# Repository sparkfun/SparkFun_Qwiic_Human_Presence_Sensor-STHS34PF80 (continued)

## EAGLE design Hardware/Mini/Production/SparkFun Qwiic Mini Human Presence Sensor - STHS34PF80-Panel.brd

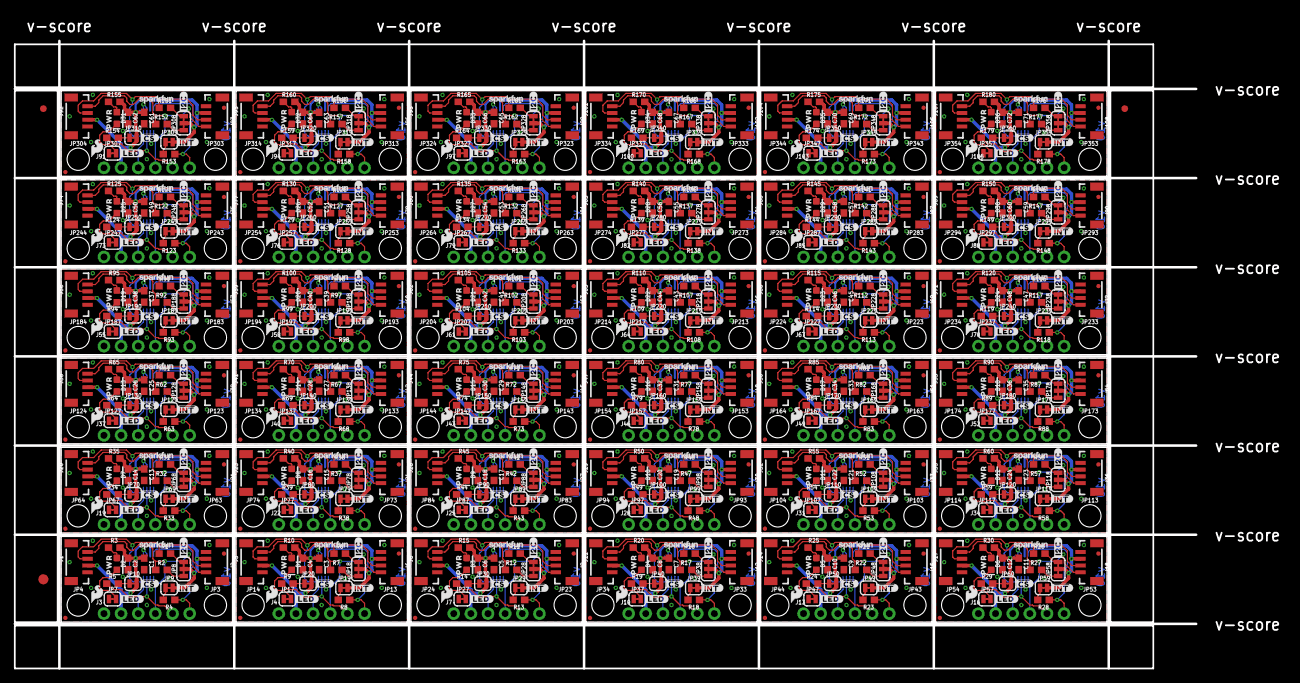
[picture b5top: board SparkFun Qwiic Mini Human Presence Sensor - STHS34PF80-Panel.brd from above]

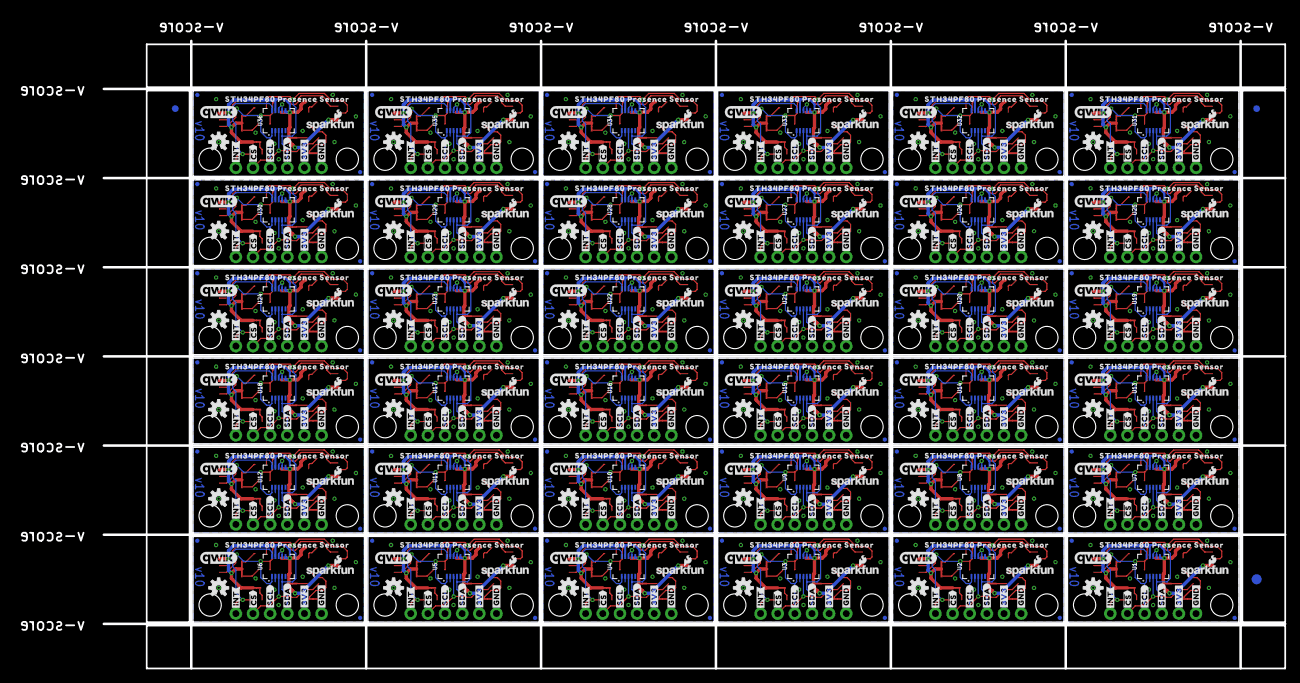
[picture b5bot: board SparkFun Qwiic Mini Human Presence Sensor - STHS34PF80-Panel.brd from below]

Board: 2 copper layers, 175.0 x 93.0 mm, 1410 parts (471 on the bottom side), 432 nets.

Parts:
C1, C3, C5, C7, C9, C11, C13, C15, C17, C19, C21, C23, C25, C27, C29, C31, C33, C35, C37, C39, C41, C43, C45, C47, C49, C51, C53, C55, C57, C59, C61, C63, C65, C67, C69, C71: 1.0uF; 0603
C2, C4, C6, C8, C10, C12, C14, C16, C18, C20, C22, C24, C26, C28, C30, C32, C34, C36, C38, C40, C42, C44, C46, C48, C50, C52, C54, C56, C58, C60, C62, C64, C66, C68, C70, C72: 0.1uF; 0603
D1, D2, D3, D4, D5, D6, D7, D8, D9, D10, D11, D12, D13, D14, D15, D16, D17, D18, D19, D20, D21, D22, D23, D24, D25, D26, D27, D28, D29, D30, D31, D32, D33, D34, D35, D36: RED; LED-0603
E$1, E$2, E$3, E$4: FIDUCIAL-1X2
E$5, E$6: FIDUCIAL-1.5X3
J1, J2, J5, J6, J8, J9, J11, J12, J14, J15, J17, J18, J20, J21, J23, J24, J26, J27, J29, J30, J32, J33, J35, J36, J38, J39, J41, J42, J44, J45, J47, J48, J50, J51, J53, J54, J56, J57, J59, J60, J62, J63, J65, J66, J68, J69, J71, J72, J74, J75, J77, J78, J80, J81, J83, J84, J86, J87, J89, J90, J92, J93, J95, J96, J98, J99, J101, J102, J104, J105, J107, J108: Vertical Qwiic Connector; JST04_1MM_VERT
J3, J4, J7, J10, J13, J16, J19, J22, J25, J28, J31, J34, J37, J40, J43, J46, J49, J52, J55, J58, J61, J64, J67, J70, J73, J76, J79, J82, J85, J88, J91, J94, J97, J100, J103, J106: 1X06_NO_SILK
JP1, JP2, JP5, JP6, JP11, JP12, JP15, JP16, JP21, JP22, JP25, JP26, JP31, JP32, JP35, JP36, JP41, JP42, JP45, JP46, JP51, JP52, JP55, JP56, JP61, JP62, JP65, JP66, JP71, JP72, JP75, JP76, JP81, JP82, JP85, JP86, JP91, JP92, JP95, JP96, JP101, JP102, JP105, JP106, JP111, JP112, JP115, JP116, JP121, JP122, JP125, JP126, JP131, JP132, JP135, JP136, JP141, JP142, JP145, JP146, JP151, JP152, JP155, JP156, JP161, JP162, JP165, JP166, JP171, JP172, JP175, JP176, JP181, JP182, JP185, JP186, JP191, JP192, JP195, JP196, JP201, JP202, JP205, JP206, JP211, JP212, JP215, JP216, JP221, JP222, JP225, JP226, JP231, JP232, JP235, JP236, JP241, JP242, JP245, JP246, JP251, JP252, JP255, JP256, JP261, JP262, JP265, JP266, JP271, JP272, JP275, JP276, JP281, JP282, JP285, JP286, JP291, JP292, JP295, JP296, JP301, JP302, JP305, JP306, JP311, JP312, JP315, JP316, JP321, JP322, JP325, JP326, JP331, JP332, JP335, JP336, JP341, JP342, JP345, JP346, JP351, JP352, JP355, JP356: FIDUCIALUFIDUCIAL; FIDUCIAL-MICRO
JP3, JP4, JP13, JP14, JP23, JP24, JP33, JP34, JP43, JP44, JP53, JP54, JP63, JP64, JP73, JP74, JP83, JP84, JP93, JP94, JP103, JP104, JP113, JP114, JP123, JP124, JP133, JP134, JP143, JP144, JP153, JP154, JP163, JP164, JP173, JP174, JP183, JP184, JP193, JP194, JP203, JP204, JP213, JP214, JP223, JP224, JP233, JP234, JP243, JP244, JP253, JP254, JP263, JP264, JP273, JP274, JP283, JP284, JP293, JP294, JP303, JP304, JP313, JP314, JP323, JP324, JP333, JP334, JP343, JP344, JP353, JP354: STAND-OFF
JP7, JP9, JP10, JP17, JP19, JP20, JP27, JP29, JP30, JP37, JP39, JP40, JP47, JP49, JP50, JP57, JP59, JP60, JP67, JP69, JP70, JP77, JP79, JP80, JP87, JP89, JP90, JP97, JP99, JP100, JP107, JP109, JP110, JP117, JP119, JP120, JP127, JP129, JP130, JP137, JP139, JP140, JP147, JP149, JP150, JP157, JP159, JP160, JP167, JP169, JP170, JP177, JP179, JP180, JP187, JP189, JP190, JP197, JP199, JP200, JP207, JP209, JP210, JP217, JP219, JP220, JP227, JP229, JP230, JP237, JP239, JP240, JP247, JP249, JP250, JP257, JP259, JP260, JP267, JP269, JP270, JP277, JP279, JP280, JP287, JP289, JP290, JP297, JP299, JP300, JP307, JP309, JP310, JP317, JP319, JP320, JP327, JP329, JP330, JP337, JP339, JP340, JP347, JP349, JP350, JP357, JP359, JP360: JUMPER-SMT_2_NC_TRACE_SILK; SMT-JUMPER_2_NC_TRACE_SILK
JP8, JP18, JP28, JP38, JP48, JP58, JP68, JP78, JP88, JP98, JP108, JP118, JP128, JP138, JP148, JP158, JP168, JP178, JP188, JP198, JP208, JP218, JP228, JP238, JP248, JP258, JP268, JP278, JP288, JP298, JP308, JP318, JP328, JP338, JP348, JP358: JUMPER-SMT_3_2-NC_TRACE_SILK; SMT-JUMPER_3_2-NC_TRACE_SILK
LOGO1, LOGO5, LOGO11, LOGO16, LOGO21, LOGO26, LOGO31, LOGO36, LOGO41, LOGO46, LOGO51, LOGO56, LOGO61, LOGO66, LOGO71, LOGO76, LOGO81, LOGO86, LOGO91, LOGO96, LOGO101, LOGO106, LOGO111, LOGO116, LOGO121, LOGO126, LOGO131, LOGO136, LOGO141, LOGO146, LOGO151, LOGO156, LOGO161, LOGO166, LOGO171, LOGO176: OSHW-LOGOS; OSHW-LOGO-S
LOGO2, LOGO8, LOGO13, LOGO18, LOGO23, LOGO28, LOGO33, LOGO38, LOGO43, LOGO48, LOGO53, LOGO58, LOGO63, LOGO68, LOGO73, LOGO78, LOGO83, LOGO88, LOGO93, LOGO98, LOGO103, LOGO108, LOGO113, LOGO118, LOGO123, LOGO128, LOGO133, LOGO138, LOGO143, LOGO148, LOGO153, LOGO158, LOGO163, LOGO168, LOGO173, LOGO178: SFE_LOGO_NAME_FLAME7_MM; SFE_LOGO_NAME_FLAME_7MM
LOGO3, LOGO7, LOGO12, LOGO17, LOGO22, LOGO27, LOGO32, LOGO37, LOGO42, LOGO47, LOGO52, LOGO57, LOGO62, LOGO67, LOGO72, LOGO77, LOGO82, LOGO87, LOGO92, LOGO97, LOGO102, LOGO107, LOGO112, LOGO117, LOGO122, LOGO127, LOGO132, LOGO137, LOGO142, LOGO147, LOGO152, LOGO157, LOGO162, LOGO167, LOGO172, LOGO177: QWIIC_LOGO_CONNECTOR; QWIIC_5.5MM
LOGO4, LOGO10, LOGO15, LOGO20, LOGO25, LOGO30, LOGO35, LOGO40, LOGO45, LOGO50, LOGO55, LOGO60, LOGO65, LOGO70, LOGO75, LOGO80, LOGO85, LOGO90, LOGO95, LOGO100, LOGO105, LOGO110, LOGO115, LOGO120, LOGO125, LOGO130, LOGO135, LOGO140, LOGO145, LOGO150, LOGO155, LOGO160, LOGO165, LOGO170, LOGO175, LOGO180: SFE_LOGO_NAME5_MM; SFE_LOGO_NAME_5MM
LOGO6, LOGO9, LOGO14, LOGO19, LOGO24, LOGO29, LOGO34, LOGO39, LOGO44, LOGO49, LOGO54, LOGO59, LOGO64, LOGO69, LOGO74, LOGO79, LOGO84, LOGO89, LOGO94, LOGO99, LOGO104, LOGO109, LOGO114, LOGO119, LOGO124, LOGO129, LOGO134, LOGO139, LOGO144, LOGO149, LOGO154, LOGO159, LOGO164, LOGO169, LOGO174, LOGO179: SFE_LOGO_FLAME.1_INCH; SFE_LOGO_FLAME_.1
R1, R2, R6, R7, R11, R12, R16, R17, R21, R22, R26, R27, R31, R32, R36, R37, R41, R42, R46, R47, R51, R52, R56, R57, R61, R62, R66, R67, R71, R72, R76, R77, R81, R82, R86, R87, R91, R92, R96, R97, R101, R102, R106, R107, R111, R112, R116, R117, R121, R122, R126, R127, R131, R132, R136, R137, R141, R142, R146, R147, R151, R152, R156, R157, R161, R162, R166, R167, R171, R172, R176, R177: 2.2k; 0603
R3, R10, R15, R20, R25, R30, R35, R40, R45, R50, R55, R60, R65, R70, R75, R80, R85, R90, R95, R100, R105, R110, R115, R120, R125, R130, R135, R140, R145, R150, R155, R160, R165, R170, R175, R180: 4.7k; 0603
R4, R5, R8, R9, R13, R14, R18, R19, R23, R24, R28, R29, R33, R34, R38, R39, R43, R44, R48, R49, R53, R54, R58, R59, R63, R64, R68, R69, R73, R74, R78, R79, R83, R84, R88, R89, R93, R94, R98, R99, R103, R104, R108, R109, R113, R114, R118, R119, R123, R124, R128, R129, R133, R134, R138, R139, R143, R144, R148, R149, R153, R154, R158, R159, R163, R164, R168, R169, R173, R174, R178, R179: 10k; 0603
U1, U2, U3, U4, U5, U6, U7, U8, U9, U10, U11, U12, U13, U14, U15, U16, U17, U18, U19, U20, U21, U22, U23, U24, U25, U26, U27, U28, U29, U30, U31, U32, U33, U34, U35, U36: STHS34PF80; OLGA-10L
U$1, U$22, U$34, U$46, U$58, U$70, U$82, U$94, U$106, U$118, U$130, U$142, U$154, U$166, U$178, U$190, U$202, U$214, U$226, U$238, U$250, U$262, U$274, U$286, U$298, U$310, U$322, U$334, U$346, U$358, U$370, U$382, U$394, U$406, U$418, U$430: #3V3#36
U$2, U$23, U$35, U$47, U$59, U$71, U$83, U$95, U$107, U$119, U$131, U$143, U$155, U$167, U$179, U$191, U$203, U$215, U$227, U$239, U$251, U$263, U$275, U$287, U$299, U$311, U$323, U$335, U$347, U$359, U$371, U$383, U$395, U$407, U$419, U$431: ##CS#36
U$3, U$6, U$25, U$37, U$49, U$61, U$73, U$85, U$97, U$109, U$121, U$133, U$145, U$157, U$169, U$181, U$193, U$205, U$217, U$229, U$241, U$253, U$265, U$277, U$289, U$301, U$313, U$325, U$337, U$349, U$361, U$373, U$385, U$397, U$409, U$421: #SDA#5
U$4, U$14, U$26, U$38, U$50, U$62, U$74, U$86, U$98, U$110, U$122, U$134, U$146, U$158, U$170, U$182, U$194, U$206, U$218, U$230, U$242, U$254, U$266, U$278, U$290, U$302, U$314, U$326, U$338, U$350, U$362, U$374, U$386, U$398, U$410, U$422: #SCL#6
U$5, U$24, U$36, U$48, U$60, U$72, U$84, U$96, U$108, U$120, U$132, U$144, U$156, U$168, U$180, U$192, U$204, U$216, U$228, U$240, U$252, U$264, U$276, U$288, U$300, U$312, U$324, U$336, U$348, U$360, U$372, U$384, U$396, U$408, U$420, U$432: #INT#37
U$7, U$15, U$27, U$39, U$51, U$63, U$75, U$87, U$99, U$111, U$123, U$135, U$147, U$159, U$171, U$183, U$195, U$207, U$219, U$231, U$243, U$255, U$267, U$279, U$291, U$303, U$315, U$327, U$339, U$351, U$363, U$375, U$387, U$399, U$411, U$423: PWR9
U$8, U$16, U$28, U$40, U$52, U$64, U$76, U$88, U$100, U$112, U$124, U$136, U$148, U$160, U$172, U$184, U$196, U$208, U$220, U$232, U$244, U$256, U$268, U$280, U$292, U$304, U$316, U$328, U$340, U$352, U$364, U$376, U$388, U$400, U$412, U$424: #I2C#0
U$9, U$17, U$29, U$41, U$53, U$65, U$77, U$89, U$101, U$113, U$125, U$137, U$149, U$161, U$173, U$185, U$197, U$209, U$221, U$233, U$245, U$257, U$269, U$281, U$293, U$305, U$317, U$329, U$341, U$353, U$365, U$377, U$389, U$401, U$413, U$425: ##CS#6
U$10, U$18, U$30, U$42, U$54, U$66, U$78, U$90, U$102, U$114, U$126, U$138, U$150, U$162, U$174, U$186, U$198, U$210, U$222, U$234, U$246, U$258, U$270, U$282, U$294, U$306, U$318, U$330, U$342, U$354, U$366, U$378, U$390, U$402, U$414, U$426: #LED#8
U$11, U$19, U$31, U$43, U$55, U$67, U$79, U$91, U$103, U$115, U$127, U$139, U$151, U$163, U$175, U$187, U$199, U$211, U$223, U$235, U$247, U$259, U$271, U$283, U$295, U$307, U$319, U$331, U$343, U$355, U$367, U$379, U$391, U$403, U$415, U$427: ##INT#9
U$12, U$20, U$32, U$44, U$56, U$68, U$80, U$92, U$104, U$116, U$128, U$140, U$152, U$164, U$176, U$188, U$200, U$212, U$224, U$236, U$248, U$260, U$272, U$284, U$296, U$308, U$320, U$332, U$344, U$356, U$368, U$380, U$392, U$404, U$416, U$428: STH34PF80_PRESENCE_SENSOR10
U$13, U$21, U$33, U$45, U$57, U$69, U$81, U$93, U$105, U$117, U$129, U$141, U$153, U$165, U$177, U$189, U$201, U$213, U$225, U$237, U$249, U$261, U$273, U$285, U$297, U$309, U$321, U$333, U$345, U$357, U$369, U$381, U$393, U$405, U$417, U$429: #GND#35

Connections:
3.3V: C1.1, C2.1, J1.2, J2.2, J3.2, JP8.2, JP9.2, JP10.2, R3.2, U1.6, U1.9
3.3V1: C3.1, C4.1, J4.2, J5.2, J6.2, JP18.2, JP19.2, JP20.2, R10.2, U2.6, U2.9
3.3V2: C5.1, C6.1, J7.2, J8.2, J9.2, JP28.2, JP29.2, JP30.2, R15.2, U3.6, U3.9
3.3V3: C7.1, C8.1, J10.2, J11.2, J12.2, JP38.2, JP39.2, JP40.2, R20.2, U4.6, U4.9
3.3V4: C9.1, C10.1, J13.2, J14.2, J15.2, JP48.2, JP49.2, JP50.2, R25.2, U5.6, U5.9
3.3V5: C11.1, C12.1, J16.2, J17.2, J18.2, JP58.2, JP59.2, JP60.2, R30.2, U6.6, U6.9
3.3V6: C13.1, C14.1, J19.2, J20.2, J21.2, JP68.2, JP69.2, JP70.2, R35.2, U7.6, U7.9
3.3V7: C15.1, C16.1, J22.2, J23.2, J24.2, JP78.2, JP79.2, JP80.2, R40.2, U8.6, U8.9
3.3V8: C17.1, C18.1, J25.2, J26.2, J27.2, JP88.2, JP89.2, JP90.2, R45.2, U9.6, U9.9
3.3V9: C19.1, C20.1, J28.2, J29.2, J30.2, JP98.2, JP99.2, JP100.2, R50.2, U10.6, U10.9
3.3V10: C21.1, C22.1, J31.2, J32.2, J33.2, JP108.2, JP109.2, JP110.2, R55.2, U11.6, U11.9
3.3V11: C23.1, C24.1, J34.2, J35.2, J36.2, JP118.2, JP119.2, JP120.2, R60.2, U12.6, U12.9
3.3V12: C25.1, C26.1, J37.2, J38.2, J39.2, JP128.2, JP129.2, JP130.2, R65.2, U13.6, U13.9
3.3V13: C27.1, C28.1, J40.2, J41.2, J42.2, JP138.2, JP139.2, JP140.2, R70.2, U14.6, U14.9
3.3V14: C29.1, C30.1, J43.2, J44.2, J45.2, JP148.2, JP149.2, JP150.2, R75.2, U15.6, U15.9
3.3V15: C31.1, C32.1, J46.2, J47.2, J48.2, JP158.2, JP159.2, JP160.2, R80.2, U16.6, U16.9
3.3V16: C33.1, C34.1, J49.2, J50.2, J51.2, JP168.2, JP169.2, JP170.2, R85.2, U17.6, U17.9
3.3V17: C35.1, C36.1, J52.2, J53.2, J54.2, JP178.2, JP179.2, JP180.2, R90.2, U18.6, U18.9
3.3V18: C37.1, C38.1, J55.2, J56.2, J57.2, JP188.2, JP189.2, JP190.2, R95.2, U19.6, U19.9
3.3V19: C39.1, C40.1, J58.2, J59.2, J60.2, JP198.2, JP199.2, JP200.2, R100.2, U20.6, U20.9
3.3V20: C41.1, C42.1, J61.2, J62.2, J63.2, JP208.2, JP209.2, JP210.2, R105.2, U21.6, U21.9
3.3V21: C43.1, C44.1, J64.2, J65.2, J66.2, JP218.2, JP219.2, JP220.2, R110.2, U22.6, U22.9
3.3V22: C45.1, C46.1, J67.2, J68.2, J69.2, JP228.2, JP229.2, JP230.2, R115.2, U23.6, U23.9
3.3V23: C47.1, C48.1, J70.2, J71.2, J72.2, JP238.2, JP239.2, JP240.2, R120.2, U24.6, U24.9
3.3V24: C49.1, C50.1, J73.2, J74.2, J75.2, JP248.2, JP249.2, JP250.2, R125.2, U25.6, U25.9
3.3V25: C51.1, C52.1, J76.2, J77.2, J78.2, JP258.2, JP259.2, JP260.2, R130.2, U26.6, U26.9
3.3V26: C53.1, C54.1, J79.2, J80.2, J81.2, JP268.2, JP269.2, JP270.2, R135.2, U27.6, U27.9
3.3V27: C55.1, C56.1, J82.2, J83.2, J84.2, JP278.2, JP279.2, JP280.2, R140.2, U28.6, U28.9
3.3V28: C57.1, C58.1, J85.2, J86.2, J87.2, JP288.2, JP289.2, JP290.2, R145.2, U29.6, U29.9
3.3V29: C59.1, C60.1, J88.2, J89.2, J90.2, JP298.2, JP299.2, JP300.2, R150.2, U30.6, U30.9
3.3V30: C61.1, C62.1, J91.2, J92.2, J93.2, JP308.2, JP309.2, JP310.2, R155.2, U31.6, U31.9
3.3V31: C63.1, C64.1, J94.2, J95.2, J96.2, JP318.2, JP319.2, JP320.2, R160.2, U32.6, U32.9
3.3V32: C65.1, C66.1, J97.2, J98.2, J99.2, JP328.2, JP329.2, JP330.2, R165.2, U33.6, U33.9
3.3V33: C67.1, C68.1, J100.2, J101.2, J102.2, JP338.2, JP339.2, JP340.2, R170.2, U34.6, U34.9
3.3V34: C69.1, C70.1, J103.2, J104.2, J105.2, JP348.2, JP349.2, JP350.2, R175.2, U35.6, U35.9
3.3V35: C71.1, C72.1, J106.2, J107.2, J108.2, JP358.2, JP359.2, JP360.2, R180.2, U36.6, U36.9
!CS!: J3.5, R5.1, U1.3
!CS!1: J4.5, R9.1, U2.3
!CS!2: J7.5, R14.1, U3.3
!CS!3: J10.5, R19.1, U4.3
!CS!4: J13.5, R24.1, U5.3
!CS!5: J16.5, R29.1, U6.3
!CS!6: J19.5, R34.1, U7.3
!CS!7: J22.5, R39.1, U8.3
!CS!8: J25.5, R44.1, U9.3
!CS!9: J28.5, R49.1, U10.3
!CS!10: J31.5, R54.1, U11.3
!CS!11: J34.5, R59.1, U12.3
!CS!12: J37.5, R64.1, U13.3
!CS!13: J40.5, R69.1, U14.3
!CS!14: J43.5, R74.1, U15.3
!CS!15: J46.5, R79.1, U16.3
!CS!16: J49.5, R84.1, U17.3
!CS!17: J52.5, R89.1, U18.3
!CS!18: J55.5, R94.1, U19.3
!CS!19: J58.5, R99.1, U20.3
!CS!20: J61.5, R104.1, U21.3
!CS!21: J64.5, R109.1, U22.3
!CS!22: J67.5, R114.1, U23.3
!CS!23: J70.5, R119.1, U24.3
!CS!24: J73.5, R124.1, U25.3
!CS!25: J76.5, R129.1, U26.3
!CS!26: J79.5, R134.1, U27.3
!CS!27: J82.5, R139.1, U28.3
!CS!28: J85.5, R144.1, U29.3
!CS!29: J88.5, R149.1, U30.3
!CS!30: J91.5, R154.1, U31.3
!CS!31: J94.5, R159.1, U32.3
!CS!32: J97.5, R164.1, U33.3
!CS!33: J100.5, R169.1, U34.3
!CS!34: J103.5, R174.1, U35.3
!CS!35: J106.5, R179.1, U36.3
GND: C1.2, C2.2, J1.1, J2.1, J3.1, JP7.1, U1.2, U1.7, U1.8
GND1: C3.2, C4.2, J4.1, J5.1, J6.1, JP17.1, U2.2, U2.7, U2.8
GND2: C5.2, C6.2, J7.1, J8.1, J9.1, JP27.1, U3.2, U3.7, U3.8
GND3: C7.2, C8.2, J10.1, J11.1, J12.1, JP37.1, U4.2, U4.7, U4.8
GND4: C9.2, C10.2, J13.1, J14.1, J15.1, JP47.1, U5.2, U5.7, U5.8
GND5: C11.2, C12.2, J16.1, J17.1, J18.1, JP57.1, U6.2, U6.7, U6.8
GND6: C13.2, C14.2, J19.1, J20.1, J21.1, JP67.1, U7.2, U7.7, U7.8
GND7: C15.2, C16.2, J22.1, J23.1, J24.1, JP77.1, U8.2, U8.7, U8.8
GND8: C17.2, C18.2, J25.1, J26.1, J27.1, JP87.1, U9.2, U9.7, U9.8
GND9: C19.2, C20.2, J28.1, J29.1, J30.1, JP97.1, U10.2, U10.7, U10.8
GND10: C21.2, C22.2, J31.1, J32.1, J33.1, JP107.1, U11.2, U11.7, U11.8
GND11: C23.2, C24.2, J34.1, J35.1, J36.1, JP117.1, U12.2, U12.7, U12.8
GND12: C25.2, C26.2, J37.1, J38.1, J39.1, JP127.1, U13.2, U13.7, U13.8
GND13: C27.2, C28.2, J40.1, J41.1, J42.1, JP137.1, U14.2, U14.7, U14.8
GND14: C29.2, C30.2, J43.1, J44.1, J45.1, JP147.1, U15.2, U15.7, U15.8
GND15: C31.2, C32.2, J46.1, J47.1, J48.1, JP157.1, U16.2, U16.7, U16.8
GND16: C33.2, C34.2, J49.1, J50.1, J51.1, JP167.1, U17.2, U17.7, U17.8
GND17: C35.2, C36.2, J52.1, J53.1, J54.1, JP177.1, U18.2, U18.7, U18.8
GND18: C37.2, C38.2, J55.1, J56.1, J57.1, JP187.1, U19.2, U19.7, U19.8
GND19: C39.2, C40.2, J58.1, J59.1, J60.1, JP197.1, U20.2, U20.7, U20.8
GND20: C41.2, C42.2, J61.1, J62.1, J63.1, JP207.1, U21.2, U21.7, U21.8
GND21: C43.2, C44.2, J64.1, J65.1, J66.1, JP217.1, U22.2, U22.7, U22.8
GND22: C45.2, C46.2, J67.1, J68.1, J69.1, JP227.1, U23.2, U23.7, U23.8
GND23: C47.2, C48.2, J70.1, J71.1, J72.1, JP237.1, U24.2, U24.7, U24.8
GND24: C49.2, C50.2, J73.1, J74.1, J75.1, JP247.1, U25.2, U25.7, U25.8
GND25: C51.2, C52.2, J76.1, J77.1, J78.1, JP257.1, U26.2, U26.7, U26.8
GND26: C53.2, C54.2, J79.1, J80.1, J81.1, JP267.1, U27.2, U27.7, U27.8
GND27: C55.2, C56.2, J82.1, J83.1, J84.1, JP277.1, U28.2, U28.7, U28.8
GND28: C57.2, C58.2, J85.1, J86.1, J87.1, JP287.1, U29.2, U29.7, U29.8
GND29: C59.2, C60.2, J88.1, J89.1, J90.1, JP297.1, U30.2, U30.7, U30.8
GND30: C61.2, C62.2, J91.1, J92.1, J93.1, JP307.1, U31.2, U31.7, U31.8
GND31: C63.2, C64.2, J94.1, J95.1, J96.1, JP317.1, U32.2, U32.7, U32.8
GND32: C65.2, C66.2, J97.1, J98.1, J99.1, JP327.1, U33.2, U33.7, U33.8
GND33: C67.2, C68.2, J100.1, J101.1, J102.1, JP337.1, U34.2, U34.7, U34.8
GND34: C69.2, C70.2, J103.1, J104.1, J105.1, JP347.1, U35.2, U35.7, U35.8
GND35: C71.2, C72.2, J106.1, J107.1, J108.1, JP357.1, U36.2, U36.7, U36.8
INT: J3.6, R4.1, U1.10
INT1: J4.6, R8.1, U2.10
INT2: J7.6, R13.1, U3.10
INT3: J10.6, R18.1, U4.10
INT4: J13.6, R23.1, U5.10
INT5: J16.6, R28.1, U6.10
INT6: J19.6, R33.1, U7.10
INT7: J22.6, R38.1, U8.10
INT8: J25.6, R43.1, U9.10
INT9: J28.6, R48.1, U10.10
INT10: J31.6, R53.1, U11.10
INT11: J34.6, R58.1, U12.10
INT12: J37.6, R63.1, U13.10
INT13: J40.6, R68.1, U14.10
INT14: J43.6, R73.1, U15.10
INT15: J46.6, R78.1, U16.10
INT16: J49.6, R83.1, U17.10
INT17: J52.6, R88.1, U18.10
INT18: J55.6, R93.1, U19.10
INT19: J58.6, R98.1, U20.10
INT20: J61.6, R103.1, U21.10
INT21: J64.6, R108.1, U22.10
INT22: J67.6, R113.1, U23.10
INT23: J70.6, R118.1, U24.10
INT24: J73.6, R123.1, U25.10
INT25: J76.6, R128.1, U26.10
INT26: J79.6, R133.1, U27.10
INT27: J82.6, R138.1, U28.10
INT28: J85.6, R143.1, U29.10
INT29: J88.6, R148.1, U30.10
INT30: J91.6, R153.1, U31.10
INT31: J94.6, R158.1, U32.10
INT32: J97.6, R163.1, U33.10
INT33: J100.6, R168.1, U34.10
INT34: J103.6, R173.1, U35.10
INT35: J106.6, R178.1, U36.10
unnamed: D2.C, JP7.2
unnamed: JP8.3, R1.2
unnamed: JP8.1, R2.2
unnamed: D2.A, R3.1
unnamed: JP9.1, R4.2
unnamed: JP10.1, R5.2
unnamed: JP18.3, R6.2
unnamed: JP18.1, R7.2
unnamed: D1.A, R10.1
unnamed: JP19.1, R8.2
unnamed: D1.C, JP17.2
unnamed: JP20.1, R9.2
unnamed: JP28.3, R11.2
unnamed: JP28.1, R12.2
unnamed: D3.A, R15.1
unnamed: JP29.1, R13.2
unnamed: D3.C, JP27.2
unnamed: JP30.1, R14.2
unnamed: JP38.3, R16.2
unnamed: JP38.1, R17.2
unnamed: D4.A, R20.1
unnamed: JP39.1, R18.2
unnamed: D4.C, JP37.2
unnamed: JP40.1, R19.2
unnamed: JP48.3, R21.2
unnamed: JP48.1, R22.2
unnamed: D5.A, R25.1
unnamed: JP49.1, R23.2
unnamed: D5.C, JP47.2
unnamed: JP50.1, R24.2
unnamed: JP58.3, R26.2
unnamed: JP58.1, R27.2
unnamed: D6.A, R30.1
unnamed: JP59.1, R28.2
unnamed: D6.C, JP57.2
unnamed: JP60.1, R29.2
unnamed: JP68.3, R31.2
unnamed: JP68.1, R32.2
unnamed: D7.A, R35.1
unnamed: JP69.1, R33.2
unnamed: D7.C, JP67.2
unnamed: JP70.1, R34.2
unnamed: JP78.3, R36.2
unnamed: JP78.1, R37.2
unnamed: D8.A, R40.1
unnamed: JP79.1, R38.2
unnamed: D8.C, JP77.2
unnamed: JP80.1, R39.2
unnamed: JP88.3, R41.2
unnamed: JP88.1, R42.2
unnamed: D9.A, R45.1
unnamed: JP89.1, R43.2
unnamed: D9.C, JP87.2
unnamed: JP90.1, R44.2
unnamed: JP98.3, R46.2
unnamed: JP98.1, R47.2
unnamed: D10.A, R50.1
unnamed: JP99.1, R48.2
unnamed: D10.C, JP97.2
unnamed: JP100.1, R49.2
unnamed: JP108.3, R51.2
unnamed: JP108.1, R52.2
unnamed: D11.A, R55.1
unnamed: JP109.1, R53.2
unnamed: D11.C, JP107.2
unnamed: JP110.1, R54.2
unnamed: JP118.3, R56.2
unnamed: JP118.1, R57.2
unnamed: D12.A, R60.1
unnamed: JP119.1, R58.2
unnamed: D12.C, JP117.2
unnamed: JP120.1, R59.2
unnamed: JP128.3, R61.2
unnamed: JP128.1, R62.2
unnamed: D13.A, R65.1
unnamed: JP129.1, R63.2
unnamed: D13.C, JP127.2
unnamed: JP130.1, R64.2
unnamed: JP138.3, R66.2
unnamed: JP138.1, R67.2
unnamed: D14.A, R70.1
unnamed: JP139.1, R68.2
unnamed: D14.C, JP137.2
unnamed: JP140.1, R69.2
unnamed: JP148.3, R71.2
unnamed: JP148.1, R72.2
unnamed: D15.A, R75.1
unnamed: JP149.1, R73.2
unnamed: D15.C, JP147.2
unnamed: JP150.1, R74.2
unnamed: JP158.3, R76.2
unnamed: JP158.1, R77.2
unnamed: D16.A, R80.1
unnamed: JP159.1, R78.2
unnamed: D16.C, JP157.2
unnamed: JP160.1, R79.2
unnamed: JP168.3, R81.2
unnamed: JP168.1, R82.2
unnamed: D17.A, R85.1
unnamed: JP169.1, R83.2
unnamed: D17.C, JP167.2
unnamed: JP170.1, R84.2
unnamed: JP178.3, R86.2
unnamed: JP178.1, R87.2
unnamed: D18.A, R90.1
unnamed: JP179.1, R88.2
unnamed: D18.C, JP177.2
unnamed: JP180.1, R89.2
unnamed: JP188.3, R91.2
unnamed: JP188.1, R92.2
unnamed: D19.A, R95.1
unnamed: JP189.1, R93.2
unnamed: D19.C, JP187.2
unnamed: JP190.1, R94.2
unnamed: JP198.3, R96.2
unnamed: JP198.1, R97.2
unnamed: D20.A, R100.1
unnamed: JP199.1, R98.2
unnamed: D20.C, JP197.2
unnamed: JP200.1, R99.2
unnamed: JP208.3, R101.2
unnamed: JP208.1, R102.2
unnamed: D21.A, R105.1
unnamed: JP209.1, R103.2
unnamed: D21.C, JP207.2
unnamed: JP210.1, R104.2
unnamed: JP218.3, R106.2
unnamed: JP218.1, R107.2
unnamed: D22.A, R110.1
unnamed: JP219.1, R108.2
unnamed: D22.C, JP217.2
unnamed: JP220.1, R109.2
unnamed: JP228.3, R111.2
unnamed: JP228.1, R112.2
unnamed: D23.A, R115.1
unnamed: JP229.1, R113.2
unnamed: D23.C, JP227.2
unnamed: JP230.1, R114.2
unnamed: JP238.3, R116.2
unnamed: JP238.1, R117.2
unnamed: D24.A, R120.1
unnamed: JP239.1, R118.2
unnamed: D24.C, JP237.2
unnamed: JP240.1, R119.2
unnamed: JP248.3, R121.2
unnamed: JP248.1, R122.2
unnamed: D25.A, R125.1
unnamed: JP249.1, R123.2
unnamed: D25.C, JP247.2
unnamed: JP250.1, R124.2
unnamed: JP258.3, R126.2
unnamed: JP258.1, R127.2
unnamed: D26.A, R130.1
unnamed: JP259.1, R128.2
unnamed: D26.C, JP257.2
unnamed: JP260.1, R129.2
unnamed: JP268.3, R131.2
unnamed: JP268.1, R132.2
unnamed: D27.A, R135.1
unnamed: JP269.1, R133.2
unnamed: D27.C, JP267.2
unnamed: JP270.1, R134.2
unnamed: JP278.3, R136.2
unnamed: JP278.1, R137.2
unnamed: D28.A, R140.1
unnamed: JP279.1, R138.2
unnamed: D28.C, JP277.2
unnamed: JP280.1, R139.2
unnamed: JP288.3, R141.2
unnamed: JP288.1, R142.2
unnamed: D29.A, R145.1
unnamed: JP289.1, R143.2
unnamed: D29.C, JP287.2
unnamed: JP290.1, R144.2
unnamed: JP298.3, R146.2
unnamed: JP298.1, R147.2
unnamed: D30.A, R150.1
unnamed: JP299.1, R148.2
unnamed: D30.C, JP297.2
unnamed: JP300.1, R149.2
unnamed: JP308.3, R151.2
unnamed: JP308.1, R152.2
unnamed: D31.A, R155.1
unnamed: JP309.1, R153.2
unnamed: D31.C, JP307.2
unnamed: JP310.1, R154.2
unnamed: JP318.3, R156.2
unnamed: JP318.1, R157.2
unnamed: D32.A, R160.1
unnamed: JP319.1, R158.2
unnamed: D32.C, JP317.2
unnamed: JP320.1, R159.2
unnamed: JP328.3, R161.2
unnamed: JP328.1, R162.2
unnamed: D33.A, R165.1
unnamed: JP329.1, R163.2
unnamed: D33.C, JP327.2
unnamed: JP330.1, R164.2
unnamed: JP338.3, R166.2
unnamed: JP338.1, R167.2
unnamed: D34.A, R170.1
unnamed: JP339.1, R168.2
unnamed: D34.C, JP337.2
unnamed: JP340.1, R169.2
unnamed: JP348.3, R171.2
unnamed: JP348.1, R172.2
unnamed: D35.A, R175.1
unnamed: JP349.1, R173.2
unnamed: D35.C, JP347.2
unnamed: JP350.1, R174.2
unnamed: JP358.3, R176.2
unnamed: JP358.1, R177.2
unnamed: D36.A, R180.1
unnamed: JP359.1, R178.2
unnamed: D36.C, JP357.2
unnamed: JP360.1, R179.2
SCL: J1.4, J2.4, J3.4, R2.1, U1.1
SCL1: J4.4, J5.4, J6.4, R7.1, U2.1
SCL2: J7.4, J8.4, J9.4, R12.1, U3.1
SCL3: J10.4, J11.4, J12.4, R17.1, U4.1
SCL4: J13.4, J14.4, J15.4, R22.1, U5.1
SCL5: J16.4, J17.4, J18.4, R27.1, U6.1
SCL6: J19.4, J20.4, J21.4, R32.1, U7.1
SCL7: J22.4, J23.4, J24.4, R37.1, U8.1
SCL8: J25.4, J26.4, J27.4, R42.1, U9.1
SCL9: J28.4, J29.4, J30.4, R47.1, U10.1
SCL10: J31.4, J32.4, J33.4, R52.1, U11.1
SCL11: J34.4, J35.4, J36.4, R57.1, U12.1
SCL12: J37.4, J38.4, J39.4, R62.1, U13.1
SCL13: J40.4, J41.4, J42.4, R67.1, U14.1
SCL14: J43.4, J44.4, J45.4, R72.1, U15.1
SCL15: J46.4, J47.4, J48.4, R77.1, U16.1
SCL16: J49.4, J50.4, J51.4, R82.1, U17.1
SCL17: J52.4, J53.4, J54.4, R87.1, U18.1
SCL18: J55.4, J56.4, J57.4, R92.1, U19.1
SCL19: J58.4, J59.4, J60.4, R97.1, U20.1
SCL20: J61.4, J62.4, J63.4, R102.1, U21.1
SCL21: J64.4, J65.4, J66.4, R107.1, U22.1
SCL22: J67.4, J68.4, J69.4, R112.1, U23.1
SCL23: J70.4, J71.4, J72.4, R117.1, U24.1
SCL24: J73.4, J74.4, J75.4, R122.1, U25.1
SCL25: J76.4, J77.4, J78.4, R127.1, U26.1
SCL26: J79.4, J80.4, J81.4, R132.1, U27.1
SCL27: J82.4, J83.4, J84.4, R137.1, U28.1
SCL28: J85.4, J86.4, J87.4, R142.1, U29.1
SCL29: J88.4, J89.4, J90.4, R147.1, U30.1
SCL30: J91.4, J92.4, J93.4, R152.1, U31.1
SCL31: J94.4, J95.4, J96.4, R157.1, U32.1
SCL32: J97.4, J98.4, J99.4, R162.1, U33.1
SCL33: J100.4, J101.4, J102.4, R167.1, U34.1
SCL34: J103.4, J104.4, J105.4, R172.1, U35.1
SCL35: J106.4, J107.4, J108.4, R177.1, U36.1
SDA: J1.3, J2.3, J3.3, R1.1, U1.4
SDA1: J4.3, J5.3, J6.3, R6.1, U2.4
SDA2: J7.3, J8.3, J9.3, R11.1, U3.4
SDA3: J10.3, J11.3, J12.3, R16.1, U4.4
SDA4: J13.3, J14.3, J15.3, R21.1, U5.4
SDA5: J16.3, J17.3, J18.3, R26.1, U6.4
SDA6: J19.3, J20.3, J21.3, R31.1, U7.4
SDA7: J22.3, J23.3, J24.3, R36.1, U8.4
SDA8: J25.3, J26.3, J27.3, R41.1, U9.4
SDA9: J28.3, J29.3, J30.3, R46.1, U10.4
SDA10: J31.3, J32.3, J33.3, R51.1, U11.4
SDA11: J34.3, J35.3, J36.3, R56.1, U12.4
SDA12: J37.3, J38.3, J39.3, R61.1, U13.4
SDA13: J40.3, J41.3, J42.3, R66.1, U14.4
SDA14: J43.3, J44.3, J45.3, R71.1, U15.4
SDA15: J46.3, J47.3, J48.3, R76.1, U16.4
SDA16: J49.3, J50.3, J51.3, R81.1, U17.4
SDA17: J52.3, J53.3, J54.3, R86.1, U18.4
SDA18: J55.3, J56.3, J57.3, R91.1, U19.4
SDA19: J58.3, J59.3, J60.3, R96.1, U20.4
SDA20: J61.3, J62.3, J63.3, R101.1, U21.4
SDA21: J64.3, J65.3, J66.3, R106.1, U22.4
SDA22: J67.3, J68.3, J69.3, R111.1, U23.4
SDA23: J70.3, J71.3, J72.3, R116.1, U24.4
SDA24: J73.3, J74.3, J75.3, R121.1, U25.4
SDA25: J76.3, J77.3, J78.3, R126.1, U26.4
SDA26: J79.3, J80.3, J81.3, R131.1, U27.4
SDA27: J82.3, J83.3, J84.3, R136.1, U28.4
SDA28: J85.3, J86.3, J87.3, R141.1, U29.4
SDA29: J88.3, J89.3, J90.3, R146.1, U30.4
SDA30: J91.3, J92.3, J93.3, R151.1, U31.4
SDA31: J94.3, J95.3, J96.3, R156.1, U32.4
SDA32: J97.3, J98.3, J99.3, R161.1, U33.4
SDA33: J100.3, J101.3, J102.3, R166.1, U34.4
SDA34: J103.3, J104.3, J105.3, R171.1, U35.4
SDA35: J106.3, J107.3, J108.3, R176.1, U36.4

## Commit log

2023-08-04 Folder restructure and addition of datasheet(s)
    Removed the folders from the SFE repo template that were unneeded and added the datasheet, application note, and part layout guidelines for the sensor to the documentation folder.
2023-08-07 Addition of STHS34PF80 part, schematic, and board file
    Created the new part in Eagle Library and added to project. Created schematic and board files, worked on rough drafts of each.
2023-08-09 Continued design
    Adjusted symbol and footprint to reflect the I2C AND SPI interfaces. Uploading to change name in GitHub for official product name
2023-08-15 Updates to Mini - uploading to change repo name
    Continued mini board design
2023-08-15 Removed unneeded files; finished design rule errors
    Removed the regular Qwiic files and redid the structure of the file folder. Renamed the appropriate files as well. Finished the design rule errors and routing, along with the silk screen. Should be r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
2023-08-16 Move mini files into sub folder.
2023-08-16 Add 1U files.
2023-08-17 Layout Updates
    Finished updates to layout - almost ready for design review
2023-08-18 Updated design for review and added production files for Mini
    MINI ONLY: Completed layout and worked through design errors, panelized the board, and then created Gerbers for production. Added more comments throughout layout and schematic.
2023-08-18 Updated version number on schematic
    Board is now ready for review
2023-08-21 Updated files for design review
    Changed ST part to have 80% solder cream; changed panels to be 6x6 boards; changed vector font issues in schematic; added measures; added some more silk for easier part identification
2023-08-21 Removed unneeded library file
    Deleted second library for less confusion since the part that is being used is in the main Hardware library
2023-08-21 Changed from Qwiic horizontal to qwiic vertical
    Changed to the Qwiic Vertical connector we have for a better surface mounting option for the user. Updated the gerbers and panel to now have the correct information
2023-08-22 Small documentation additions
    Added I2C address to schematic and units for measures (measures in inches)
2023-09-06 Updated 1U to correct paste layer for main IC
    Updated the board and the panel/gerbers to have the correct percentage of fill for the solder paste on the STHS34PF80
2023-09-20 Update to Mini board
    Changed silkscreen on the back to have the correct part number on it
2023-10-17 Add design files for product launch
2023-10-17 Add component documentation
    Move files to proper file directory
2023-10-26 Update README.md
    Add product description
    Update links
2023-11-07 Deploy hookup guide
    Redeploy files
2023-11-07 Deployed b6d3ccd with MkDocs version: 1.5.3
2024-07-16 Fix typo
    Remove carriage return
2024-07-16 Rename file
    Renamed image file for SparkFun logo
2024-07-16 Add glossary terms
    Add glossary for abreviations
2024-07-16 Update CSS for video containers
    Modify styling for video containers
    Add QR code for Qwiic video
2024-07-16 Rename file
    Fix typo in file name
2024-07-16 Fix relative links
2024-07-16 Fix annotation
    Annotations do not function in tables
2024-07-16 Update hardware_overview.md
    Fix Qwiic banner
2024-07-16 Fix CS jumper info
    Misinterpreted schematic. The CS jumper doesn't need to be cut to enable SPI; pin just needs to be pulled low.
2024-07-16 Update extra.css
    Updates CSS to latest iteration
2024-07-16 Update mkdocs.yml
    Updates the MkDocs configuration to the latest iteration
2024-07-16 Add bug admonition
    Added notification for users on GitHub issue
2024-07-16 Update provided resources
    Rename application note files
    Update resources to include application notes
2024-07-16 Update hardware_overview.md
    Add info for operation modes and smart algorithms
2024-07-16 Add hookup guide thumbnail
2024-07-16 Update mkdocs.yml
    Update workflows for MkDocs configuration changes
2024-08-06 Change file type
2024-08-06 Deployed 3234a5d with MkDocs version: 1.6.0
2026-06-03 Deployed 44ec023 with MkDocs version: 1.6.1
